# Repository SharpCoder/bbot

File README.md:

# bbot

bbot - or balancing robot - is a two-wheeled, 3D printed robot which is capable of balancing just like a seguway. The general concept behind the algorithm is: if you are falling forward, move forward. If you are falling backward, move backward. The real challenge comes in doing this quickly and accurately enough.

## Components

The main components for bbot are as follows:

 - Adafruit Metro Mini (Arduino)
 - ADXL335 (Accelerometer)
 - SparkFun OpenLog (Telemetry to SDCard)
 - 595N (Shift Register)
 - 2x L293D (H-Bridge)
 - 2x Stepper Motors

## Project Files

The project is split out into different folders. Each folder is responsible for a different aspect of the robot design.

 - **bbot-firmware**: _The arduino source code_
 - **bbot-jupyter**: _A jupyter notebook used to analyze sensor readings_
 - **bbot-models**: _SolidWorks models, as well as finalized STL files_
 - **bbot-pcb**: _KiCAD circuit board and gerber files_

## bbot-firmware

### Overview

The algorithm which is currently implemented takes the approach of measuring the accelerometer sensor readings every 30ms and then comparing the observed values with a known threshold. If the readings indicate it is tilting forward, the robot will activate the step-forward routine for each motor. If the readings indicate it is tilting backward, the robot will activate the step-backward routine for each motor.

In order to actually move the motors, two primary files are responsible. The first being `motors.h` and `motors.cpp`. This code is designed to track which phase of each motor is active at any point in time. Knowing what phase is active allows us to determine what move to take in order to transition to a forward or backward step state. The H-Bridge is actually wired up to a shift register and to activate it, we must keep track of which pins are active in the shift register. The code which handles this is in the files `shift.h` and `shift.cpp`. Managing the shift register is relatively straightforward and simply requires sending an int array containing the state of each pin.

Collecting telemetry is an important part of this project, so that the thresholds can be tweaked in order to improve the algorithm. The `logger.h` and `logger.cpp` files are responsible for this. By leveraging a Sparkfun OpenLog, we are able to stream telemetry data to an SDCard. Each time the sensor is observed, its readings are written to the SDCard.

### Building

You can build the code through the arduino IDE. The microcontroller I used is the Adafruit Metro Mini, which is compatible with most Arduino board targets (for example: Arduino Pro Mini).

## Jupyter Notebook

## 3D Models
TBD

## Assembly Instructions
TBD

## License

All source code and models are provided under the MIT license.

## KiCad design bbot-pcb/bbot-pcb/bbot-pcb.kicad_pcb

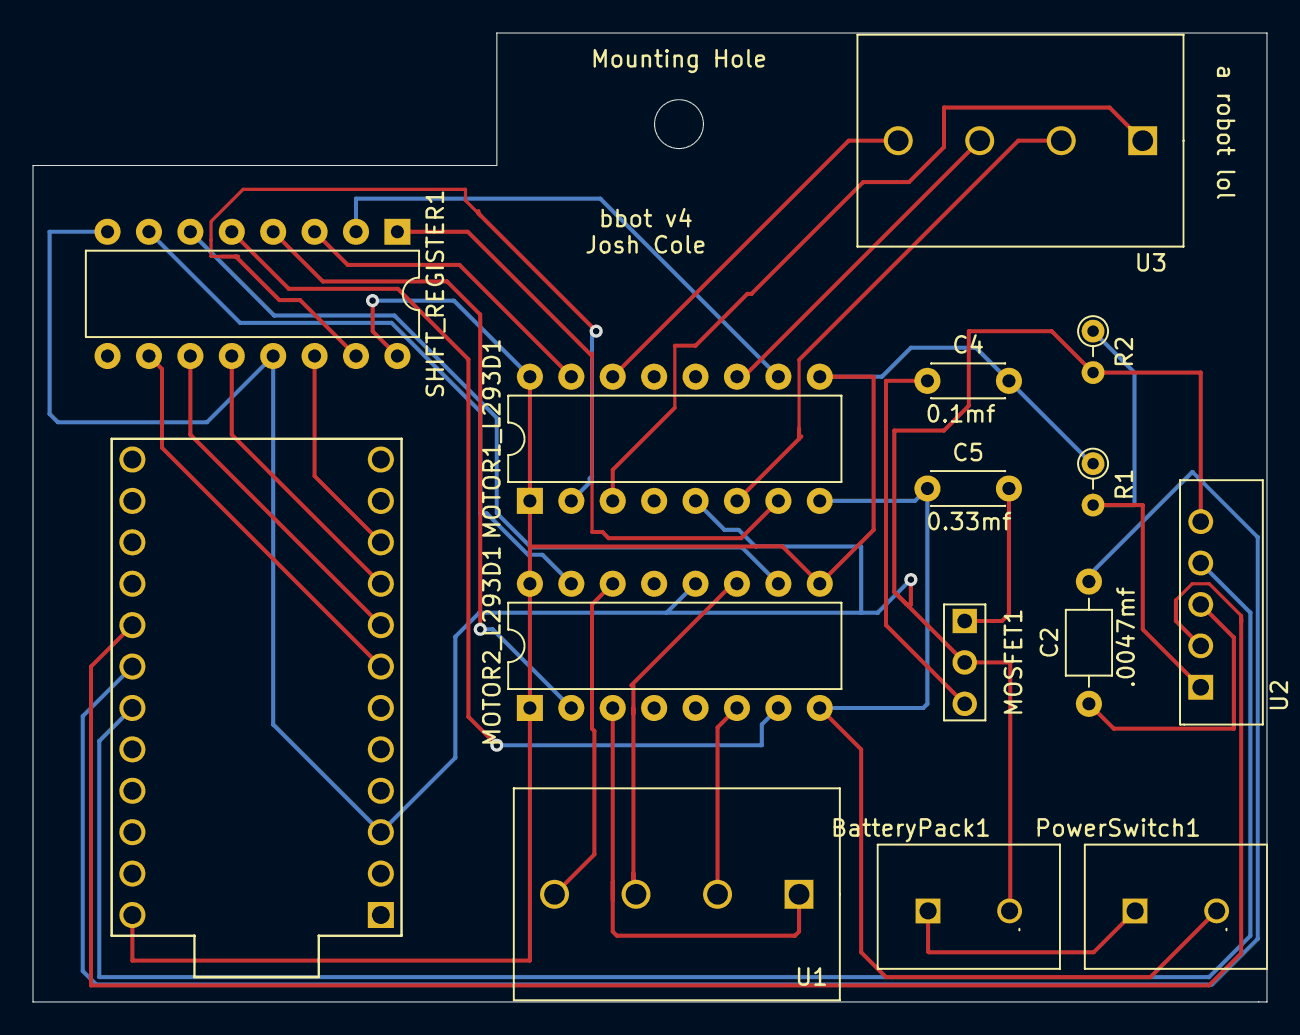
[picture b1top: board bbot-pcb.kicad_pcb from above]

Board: 2 copper layers, 75.7 x 59.4 mm, 16 parts (0 on the bottom side), 31 nets.

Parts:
BatteryPack1: Screw_Terminal_2
C2: C.0047mf; C_Axial_L3.8mm_D2.6mm_P7.50mm_Horizontal
C4: L7805_OUT_CAP; C_Disc_D4.3mm_W1.9mm_P5.00mm
C5: L7805_IN_CAP; C_Disc_D4.3mm_W1.9mm_P5.00mm
MOSFET1: L7805; L7805-A
MOTOR1_L293D1, MOTOR2_L293D1: L293D; DIP-16_W7.62mm
Mounting Hole: MountingHole_3mm
PowerSwitch1: Screw_Terminal_2
R1, R2: SPARKFUN-RESISTORS_4.7KOHM-0603-1_10W-1%; R_Axial_DIN0204_L3.6mm_D1.6mm_P2.54mm_Vertical
SHIFT_REGISTER1: 74HC595; DIP-16_W7.62mm
U1, U3: HA-552-4P; HA-522P-Latch_Terminal
U2: ADXL335
U4: ArduinoProMicro; ProMicro

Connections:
/3V: R1.2, R2.1, U2.1
/5V: C4.2, MOTOR1_L293D1.1, MOTOR1_L293D1.9, MOTOR1_L293D1.16, MOTOR2_L293D1.1, MOTOR2_L293D1.9, MOTOR2_L293D1.16, R1.1, SHIFT_REGISTER1.16, U4.24
/12V: C5.1, MOTOR1_L293D1.8, MOTOR2_L293D1.8, PowerSwitch1.2
/A0: U2.2, U4.17
/A1: C2.2, U4.18
/A2: U2.4, U4.19
/GND: BatteryPack1.2, MOSFET1.2, MOTOR1_L293D1.5, MOTOR2_L293D1.12, R2.2, SHIFT_REGISTER1.8, SHIFT_REGISTER1.13, U2.5, U4.3
/MOTOR1_A: MOTOR1_L293D1.2, SHIFT_REGISTER1.15
/MOTOR1_B: MOTOR1_L293D1.7, SHIFT_REGISTER1.1
/MOTOR1_C: MOTOR1_L293D1.10, SHIFT_REGISTER1.2
/MOTOR1_D: MOTOR1_L293D1.15, SHIFT_REGISTER1.3
/MOTOR1_PHASE_A: MOTOR1_L293D1.3, U3.1
/MOTOR1_PHASE_B: MOTOR1_L293D1.6, U3.2
/MOTOR1_PHASE_C: MOTOR1_L293D1.11, U3.3
/MOTOR1_PHASE_D: MOTOR1_L293D1.14, U3.4
/MOTOR2_A: MOTOR2_L293D1.2, SHIFT_REGISTER1.4
/MOTOR2_B: MOTOR2_L293D1.7, SHIFT_REGISTER1.5
/MOTOR2_C: MOTOR2_L293D1.10, SHIFT_REGISTER1.6
/MOTOR2_D: MOTOR2_L293D1.15, SHIFT_REGISTER1.7
/MOTOR2_PHASE_A: MOTOR2_L293D1.3, U1.1
/MOTOR2_PHASE_B: MOTOR2_L293D1.6, U1.2
/MOTOR2_PHASE_C: MOTOR2_L293D1.11, U1.3
/MOTOR2_PHASE_D: MOTOR2_L293D1.14, U1.4
/SHIFT_CLCK: SHIFT_REGISTER1.11, U4.8
/SHIFT_CLR: SHIFT_REGISTER1.10, U4.7
/SHIFT_DATA: SHIFT_REGISTER1.14, U4.10
/SHIFT_LATCH: SHIFT_REGISTER1.12, U4.9
unnamed: BatteryPack1.1, PowerSwitch1.1
unnamed: C2.1, U2.3
unnamed: C4.1, MOSFET1.3
unnamed: C5.2, MOSFET1.1

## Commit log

2021-04-04 initial commit of project code with some helper functions for motor movement
2021-04-04 implement shift register logic
2021-04-05 fix bugs with the shift register so it is fully addressable
2021-04-05 update docstrings
2021-04-05 initial commit of primary chassis and accompanying cosmetic models
2021-04-05 initial half-baked version of upper deck
2021-04-06 Add cosmetic battery pack and accompanying battery mount component
2021-04-06 Update battery mount and final assembly. begin cosmetic components for electronics
2021-04-06 initial kicad design files
2021-04-06 mostly completed library of components for the schematic
2021-04-07 unverified prototype of completed circuit board design. not quite ready to ship off to a fab yet
2021-04-08 Update firmware to support HMC5883L compass
2021-04-08 Add i2c docstrings
2021-04-08 Add docstring for the compass code
2021-04-08 Add a questionable mechanism for non-blocking delays. This will be revisited
2021-04-08 finalize kicad circuit board.
2021-04-09 some tweaks to the models and output the STL files
2021-04-09 create a wheel mounting part which is compatible with my wheels and supports affixing to the wheel and attaching to the motor via a set screw
2021-04-09 update to assembly models
2021-04-12 Add some jupyter notebook for calibrating the accelerometer
2021-04-12 Improve the battery mount and adjacent hardware
2021-04-12 OKAY! Improve the compass and timer subsystem.
    This commit is fairly huge. It introduces the concept
    of calibrated values to the compass, as well as code
    to support the self-test functionality of the peripheral.
    By leveraging the learnings of the jupyter notebook,
    some baseline multipliers were derived which help constrain
    and interpret the compass rotation value.
2021-04-19 pcb v2 updates
2021-04-19 jupyter log findings and more test data
2021-04-19 completely refactor firmware to support new compass module and openlog interface
2021-04-20 Standardize function names. Implement majority of ai logic
2021-04-20 Configure accelerometer pins so they are inputs
2021-04-20 Rearrange README.md
2021-04-20 update gitignore
2021-04-20 remove jupyter notebook files since those readings no longer apply
2021-04-20 remove pycache
2021-04-20 Remove unused libraries, repurpose LED13 as a crash indicator
2021-04-20 update readme. update STL files
2021-04-21 Add wall guards to captive nut for deck part
2021-04-21 create and arrange middle deck for power switch and accelerometer mounting
2021-04-21 update wheel mount to support captive nut walls
2021-04-23 regenerate STL files
2021-04-24 improve size and stability of motor mount part
2021-04-24 minor tweaks to the mid deck model
2021-04-30 Update PCB to v3
2021-04-30 Update models to support wider PCB board and address a number of minor tweaks
2021-06-03 RElease-candidate of models and pcb
2021-06-05 Updates to firmware
